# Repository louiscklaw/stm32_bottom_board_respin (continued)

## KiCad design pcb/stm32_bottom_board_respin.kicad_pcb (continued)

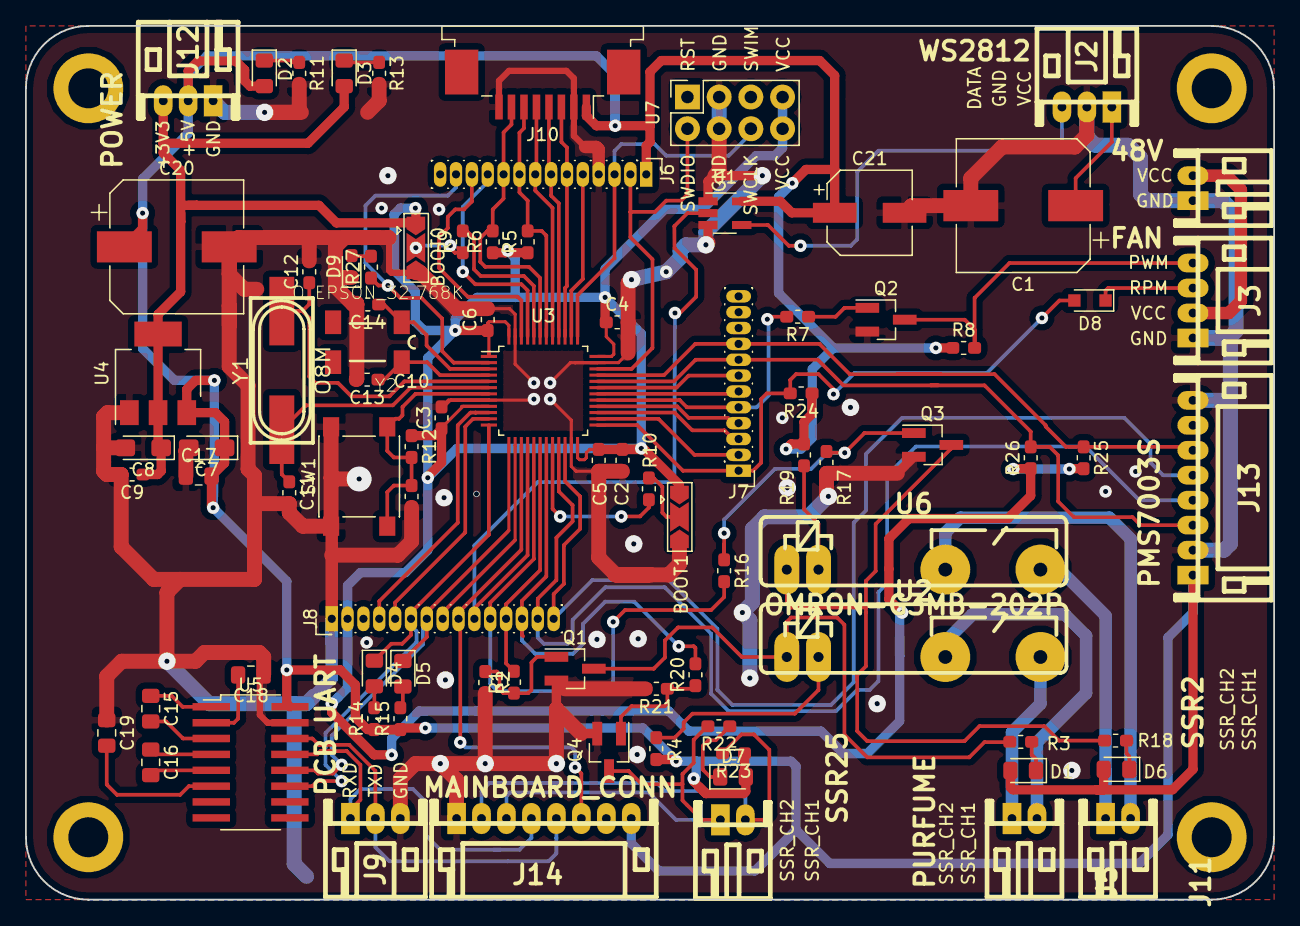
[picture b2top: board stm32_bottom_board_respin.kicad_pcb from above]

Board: 2 copper layers, 100.0 x 70.0 mm, 87 parts (0 on the bottom side), 79 nets.

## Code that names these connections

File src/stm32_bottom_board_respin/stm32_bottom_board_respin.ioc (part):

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Mcu.Name=STM32F103C(8-B)Tx
Mcu.Package=LQFP48
Mcu.UserName=STM32F103C8Tx
PA11.GPIOParameters=GPIO_Label
PA11.GPIO_Label=STM32_PMS7003S_SET
PA11.Signal=GPIO_Output
PA12.GPIOParameters=GPIO_Label
PA12.GPIO_Label=STM32_PMS7003S_RESET
PA12.Signal=GPIO_Output
PA13.Mode=Serial_Wire
PA13.Signal=SYS_JTMS-SWDIO
PA14.Mode=Serial_Wire
PA14.Signal=SYS_JTCK-SWCLK
PA2.GPIOParameters=GPIO_Label
PA2.GPIO_Label=IONAIR-TTL-TX
PA2.Mode=Asynchronous
PA2.Signal=USART2_TX
PA3.GPIOParameters=GPIO_Label
PA3.GPIO_Label=IONAIR-TTL-RX
PA3.Mode=Asynchronous
PA3.Signal=USART2_RX
PA6.GPIOParameters=GPIO_Label
PA6.GPIO_Label=STM32_WS2812_OUTPUT
PA6.Signal=S_TIM3_CH1
PA7.GPIOParameters=GPIO_Label
PA7.GPIO_Label=STM32_SSR2_OUTPUT
PA7.Signal=GPIO_Output
PA8.GPIOParameters=GPIO_Label
PA8.GPIO_Label=STM32_FAN_PWM_OUTPUT
PA8.Signal=S_TIM1_CH1
PB0.GPIOParameters=GPIO_Label
PB0.GPIO_Label=STM32_SSR1_OUTPUT
PB0.Signal=GPIO_Output
PB1.GPIOParameters=GPIO_Label
PB1.GPIO_Label=STM32_SSR-25-DA_OUTPUT
PB1.Signal=GPIO_Output
PB10.GPIOParameters=GPIO_Label
PB10.GPIO_Label=STM32_PMS7003S_TXD
PB10.Mode=Asynchronous
PB10.Signal=USART3_TX
PB11.GPIOParameters=GPIO_Label
PB11.GPIO_Label=STM32_PMS7003S_RXD
PB11.Mode=Asynchronous
PB11.Signal=USART3_RX
PB12.GPIOParameters=GPIO_Label
PB12.GPIO_Label=STM32_FAN_RPM_OUTPUT
PB12.Signal=GPIO_Input
PB3.Mode=Full_Duplex_Master
PB3.Signal=SPI1_SCK
PB4.Mode=Full_Duplex_Master
PB4.Signal=SPI1_MISO
PB5.Mode=Full_Duplex_Master
PB5.Signal=SPI1_MOSI
PB6.GPIOParameters=GPIO_Label
PB6.GPIO_Label=B2B_UART_TX
PB6.Mode=Asynchronous
PB6.Signal=USART1_TX
PB7.GPIOParameters=GPIO_Label
PB7.GPIO_Label=B2B_UART_RX
PB7.Mode=Asynchronous
PB7.Signal=USART1_RX
PC13-TAMPER-RTC.Signal=GPIO_Output
board=custom

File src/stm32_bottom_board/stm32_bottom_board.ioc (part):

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Mcu.Name=STM32F103C(8-B)Tx
Mcu.Package=LQFP48
Mcu.UserName=STM32F103C8Tx
PA13.Mode=Serial_Wire
PA13.Signal=SYS_JTMS-SWDIO
PA14.Mode=Serial_Wire
PA14.Signal=SYS_JTCK-SWCLK
PA2.Mode=Asynchronous
PA2.Signal=USART2_TX
PA3.Mode=Asynchronous
PA3.Signal=USART2_RX
PA6.Signal=S_TIM3_CH1
PB0.GPIOParameters=GPIO_Label
PB0.GPIO_Label=SSR_25_OUTPUT
PB0.Signal=GPIO_Output
PB1.GPIOParameters=GPIO_Label
PB1.GPIO_Label=PURFUME_OUTPUT
PB1.Signal=GPIO_Output
PB3.Mode=Full_Duplex_Master
PB3.Signal=SPI1_SCK
PB4.Mode=Full_Duplex_Master
PB4.Signal=SPI1_MISO
PB5.Mode=Full_Duplex_Master
PB5.Signal=SPI1_MOSI
PB6.Signal=S_TIM4_CH1
PB8.Mode=I2C
PB8.Signal=I2C1_SCL
PB9.Mode=I2C
PB9.Signal=I2C1_SDA
PD0-OSC_IN.Mode=HSE-External-Oscillator
PD0-OSC_IN.Signal=RCC_OSC_IN
PD1-OSC_OUT.Mode=HSE-External-Oscillator
PD1-OSC_OUT.Signal=RCC_OSC_OUT
RCC.SYSCLKFreq_VALUE=72000000
RCC.SYSCLKSource=RCC_SYSCLKSOURCE_PLLCLK
board=custom

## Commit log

2018-10-20 update,
2018-10-22 update to pcb directory,
2018-10-22 update,.
2018-10-27 add .gitignore .gitattributes,
2018-10-27 update 1st try photo.
2018-10-27 update FAN PWM to PA8
2018-10-27 add capacitor to the main 5V
2018-10-27 update I2C position, SPI position,
2018-10-27 update software design,
2018-10-27 update examples,
2018-10-27 fix I2C pin on PCB,
2018-10-27 update VBAT pin with 3V3,
2018-11-01 update power source terminal,
2018-11-01 update adding SSR2 on pcb and ioc,
2018-11-01 updat,
2018-11-01 update SWD_CONN pinout,
2018-11-01 categorize pinout,
2018-11-01 update to incidate the +3V3 is not necessary,
2018-11-01 align the first pin to the ground,
2018-11-01 assign footprint,
2018-11-01 init commit,
2018-11-01 update existing footprint to smaller one,
2018-11-01 fix power symbol,
2018-11-01 basic rout complete,
2018-11-01 remove jumper,
2018-11-02 add backplane from origional design
2018-11-02 sync up pcb from sch, error ignored,
2018-11-02 remove old bak file,
2018-11-02 remove uart, 232 circuit,
2018-11-02 remove old cache file,
2018-11-02 remove stm32,
2018-11-02 update J17,
2018-11-10 ignore rescue file,
2018-11-10 update gitignore,
2018-11-10 update board mounting hole,
2018-11-10 update silk label,
2018-11-22 update comments,
2018-11-22 update PCB2 done,
2018-11-22 update PCB1 done,
2018-11-22 align mounting hole,
2018-11-24 upadte,
2018-11-27 backport footprint from pcb,
2018-11-27 update pcb outline,
2018-11-27 update pcb cutout,
2018-11-29 pre-output,
2018-11-29 send to fab,
2018-12-07 update resistor for relay,
2018-12-07 update software,
2018-12-07 add optional LED power supply from main 5V,
2018-12-07 fix R14 for coil relay,
2018-12-24 update as fit for PCB,
2019-01-16 as fit resistor value to actual working value,
2019-07-06 update 3d model,
2020-05-07 ci: init travis token,
2020-05-07 ci: init travis build config,
